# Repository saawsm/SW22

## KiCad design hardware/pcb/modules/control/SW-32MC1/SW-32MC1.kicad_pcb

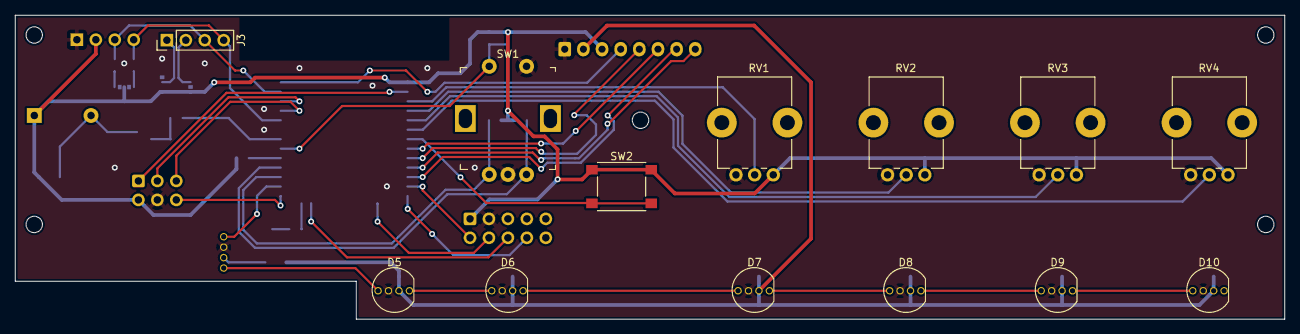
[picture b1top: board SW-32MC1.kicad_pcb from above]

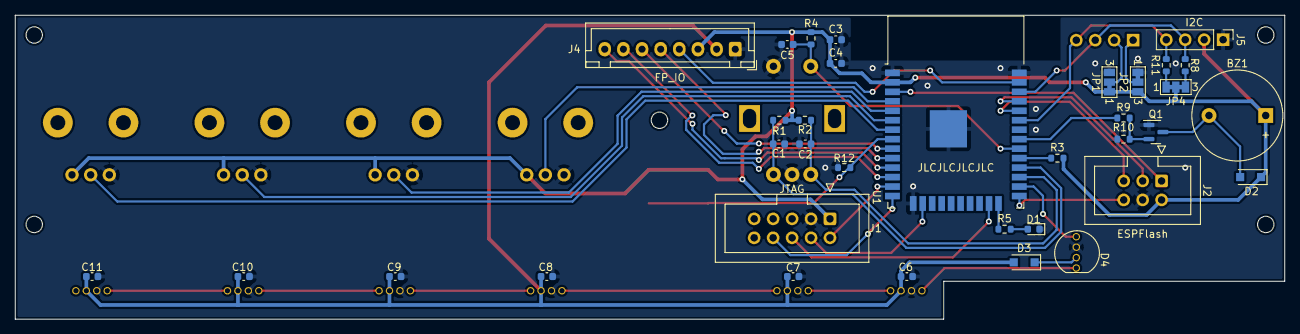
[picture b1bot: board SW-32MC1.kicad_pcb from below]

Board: 2 copper layers, 170.2 x 40.7 mm, 53 parts (35 on the bottom side), 44 nets.

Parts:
BZ1: Buzzer; Buzzer_12x9.5RM7.6
C1, C2, C5: 10nF; C_0603_1608Metric
C3: 10uF; C_0603_1608Metric
C4, C6, C7, C8, C9, C10, C11: 100nF; C_0603_1608Metric
D1: LED; LED_0603_1608Metric
D2: D_Small; D_SOD-123F
D3: D; D_SOD-123F
D4, D5, D6, D7, D8, D9, D10: WS2812D; WS2812D-F5
H1, H2, H3, H4, H5: MountingHole; MountingHole_2.2mm_M2
J1: JTAG; IDC-Header_2x05_P2.54mm_Vertical
J2: ESPFlash; IDC-Header_2x03_P2.54mm_Vertical
J3: OLED; OLED_I2C_1.3
J4: FP_IO; JST_XH_B8B-XH-A_1x08_P2.50mm_Vertical
J5: I2C; PinHeader_1x04_P2.54mm_Vertical
JP1, JP2: SolderJumper_3_Bridged12; SolderJumper-3_P1.3mm_Bridged12_Pad1.0x1.5mm_NumberLabels
JP4: SolderJumper_3_Bridged123; SolderJumper-3_P1.3mm_Bridged123_Pad1.0x1.5mm_NumberLabels
Q1: Q_NMOS_DGS; SOT-23
R1, R2, R4, R10, R12: 10K; R_0603_1608Metric
R3, R5: 10k; R_0603_1608Metric
R8, R11: 2.7K; R_0603_1608Metric
R9: 10; R_0603_1608Metric
RV1, RV2, RV3, RV4: 20K; Potentiometer_Bourns_PTV09A-1_Single_Vertical
SW1: PEC11R-4225F-S0024; Rotary_Encoder_Switched_PEC11R
SW2: DNP; SW_Push_1P1T_NO_6x6mm_H9.5mm
U1: ESP32-WROOM-32D; ESP32-WROOM-32

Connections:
+3V3: BZ1.1 (-), C3.1, C4.1, D2.1 (K), J1.1, J2.2, J4.3, J5.2, JP1.1 (A), JP2.3 (B), JP4.2 (C), R1.1, R2.1, R3.2, R4.1, RV1.1, RV2.1, RV3.1, RV4.1, SW2.1, U1.2 (VDD)
+5V: C6.2, C7.2, C8.2, C9.2, C10.2, C11.2, D3.2 (A), D5.2 (VCC), D6.2 (VCC), D7.2 (VCC), D8.2 (VCC), D9.2 (VCC), D10.2 (VCC), J4.2
/BUZZER: R9.1, U1.31 (IO19)
/EN: J2.1, U1.3 (EN)
/ENC_A: C2.1, R2.2, SW1.A, U1.27 (IO16)
/ENC_B: C1.1, R1.2, SW1.B, U1.28 (IO17)
/ENC_SW: C5.1, R4.2, SW1.S1, U1.30 (IO18)
/IO0: J2.6, U1.25 (IO0)
/IO2: R5.1, U1.24 (IO2)
/IO5: R3.1, U1.29 (IO5)
/LED_DATA: D4.4 (DIN), U1.26 (IO4)
/LINE_LEFT: J4.7, U1.12 (IO27)
/LINE_RIGHT: J4.6, U1.9 (IO33)
/LVL_A: RV1.2, U1.4 (SENSOR_VP)
/LVL_B: RV2.2, U1.5 (SENSOR_VN)
/LVL_C: RV3.2, U1.6 (IO34)
/LVL_D: RV4.2, U1.7 (IO35)
/MAIN_SCL: J4.4, U1.37 (IO23)
/MAIN_SDA: J4.5, U1.10 (IO25)
/MIC: J4.8, U1.11 (IO26)
/MTCK: J1.4, U1.16 (IO13)
/MTDI: J1.8, U1.14 (IO12)
/MTDO: J1.6, U1.23 (IO15)
/MTMS: J1.2, U1.13 (IO14)
/RXD: J2.5, U1.34 (RXD0/IO3)
/SCL: J3.3 (SCL), J5.3, R8.2, U1.36 (IO22)
/SDA: J3.4 (SDA), J5.4, R11.2, U1.33 (IO21)
/SW1: R12.1, SW2.2, U1.8 (IO32)
/TXD: J2.3, U1.35 (TXD0/IO1)
GND: C1.2, C2.2, C3.2, C4.2, C5.2, C6.1, C7.1, C8.1, C9.1, C10.1, C11.1, D1.1 (K), D4.3 (GND), D5.3 (GND), D6.3 (GND), D7.3 (GND), D8.3 (GND), D9.3 (GND), D10.3 (GND), J1.3, J2.4, J4.1, J5.1, JP1.3 (B), JP2.1 (A), Q1.1 (S), R10.2, R12.2, RV1.3, RV2.3, RV3.3, RV4.3, SW1.C, SW1.S2, U1.1 (GND), U1.15 (GND), U1.38 (GND), U1.39 (GND)
unnamed: BZ1.2 (+), D2.2 (A), Q1.3 (D)
unnamed: D1.2 (A), R5.2
unnamed: D3.1 (K), D4.2 (VCC)
unnamed: D4.1 (DOUT), D5.4 (DIN)
unnamed: D5.1 (DOUT), D6.4 (DIN)
unnamed: D6.1 (DOUT), D7.4 (DIN)
unnamed: D7.1 (DOUT), D8.4 (DIN)
unnamed: D8.1 (DOUT), D9.4 (DIN)
unnamed: D9.1 (DOUT), D10.4 (DIN)
unnamed: J3.1 (GND), JP2.2 (C)
unnamed: J3.2 (VCC), JP1.2 (C)
unnamed: JP4.1 (A), R11.1
unnamed: JP4.3 (B), R8.1
unnamed: Q1.2 (G), R9.2, R10.1

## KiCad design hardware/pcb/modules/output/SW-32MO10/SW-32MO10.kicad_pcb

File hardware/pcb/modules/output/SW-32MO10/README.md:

# SW-32MO10 - 1 Channel Output Module

## About
This is a single channel e-stim output module. It tries to mimic the output stage of the well-known Erostec ET312, or better, the MK-312.

The original design of this module was based on the design by [WendyTeslaburger/WT-312](https://github.com/WendyTeslaburger/WT-312).

## Status
- [x] Create v1.1 Schematic
- [ ] Route v1.1 PCB
- [ ] Order v1.1 PCBs
- [ ] Review 

## Gerber & Bill of Materials (BOM)
The Gerber zip file was generated with [JLCPCB](https://jlcpcb.com/) in mind (excluding assembly).
Two BOM sources are available, the interactive HTML BOM located in `/bom` folder, and a CSV file.

### Excluded BOM Items:
- 0.1" break-away pin headers/sockets
- Misc connectors

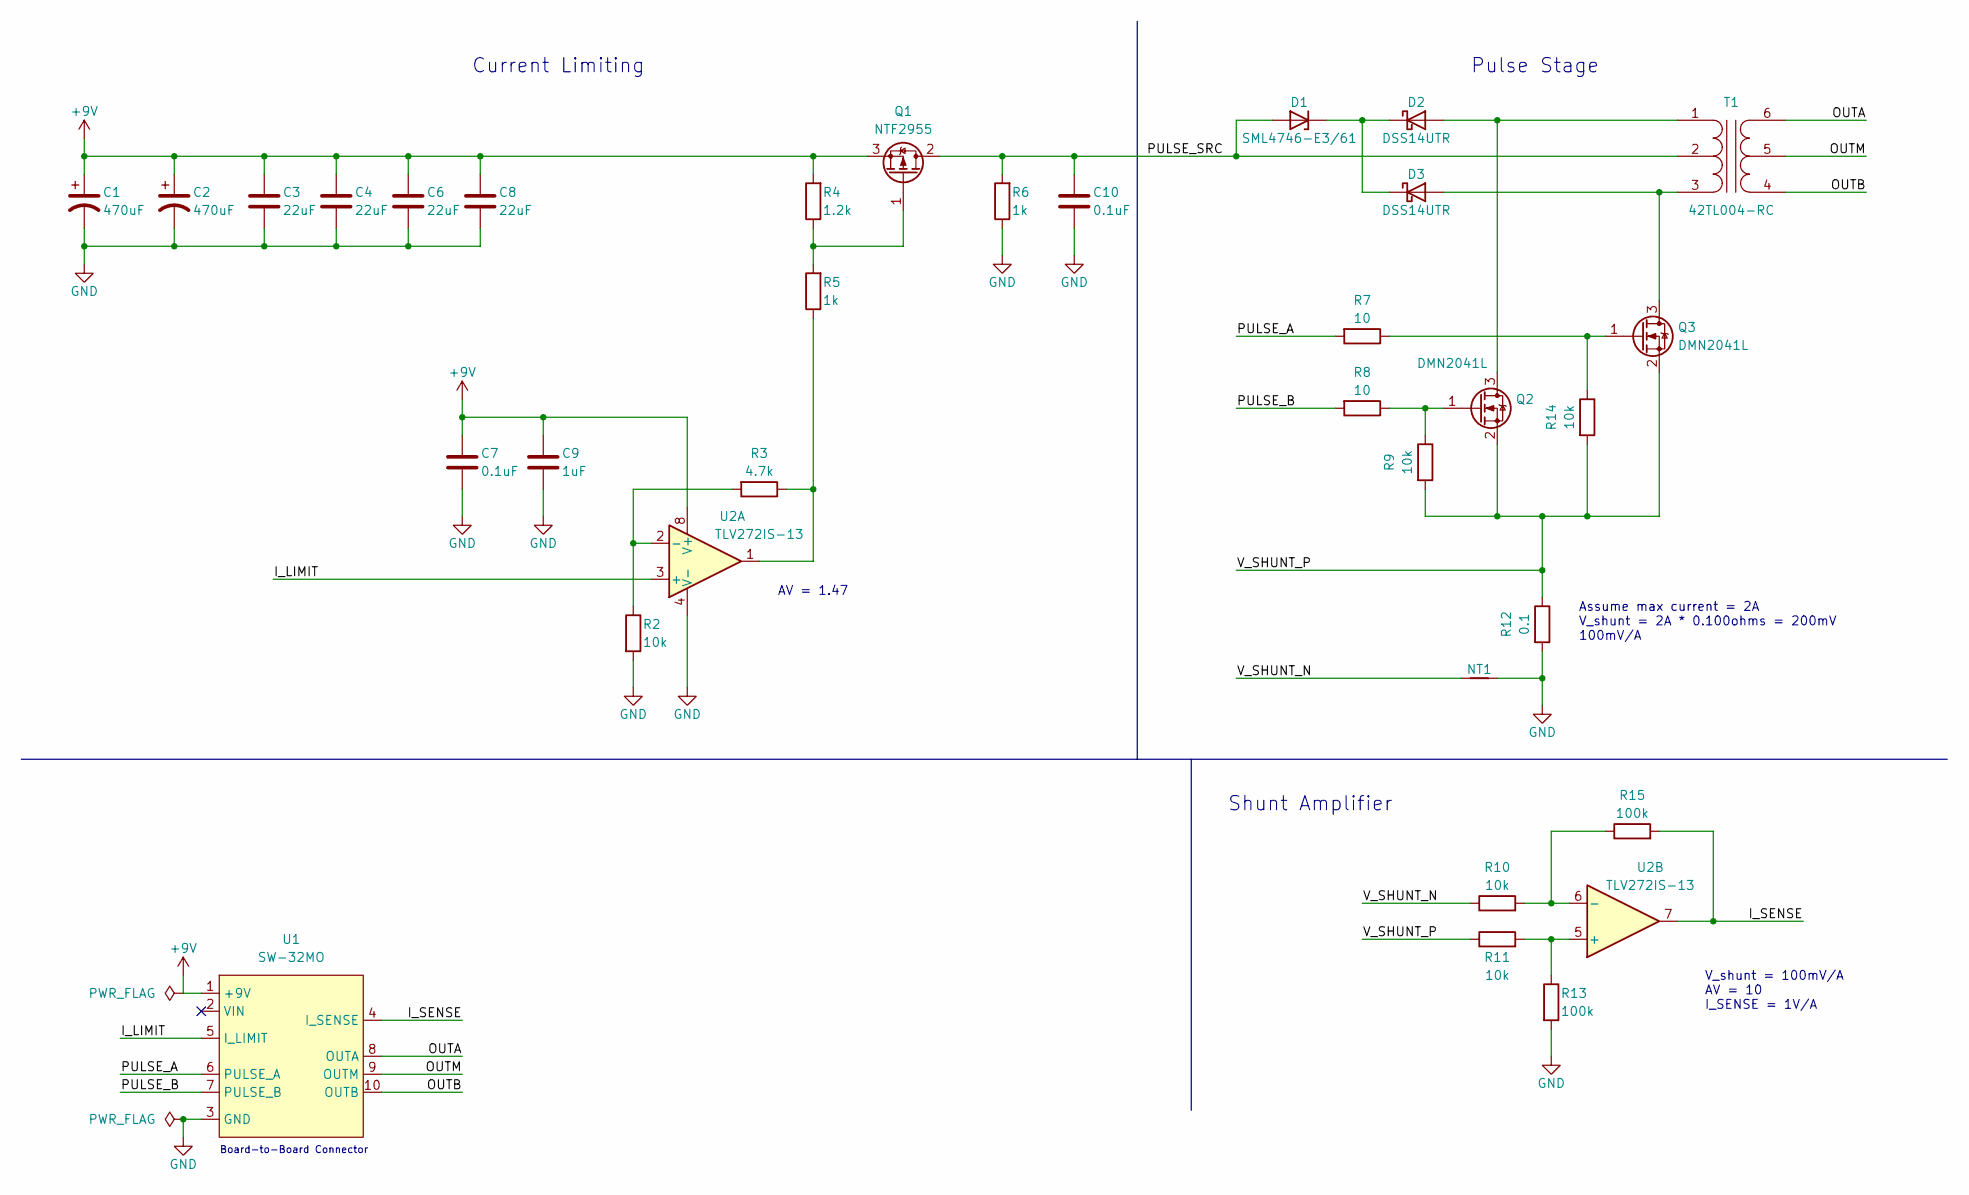
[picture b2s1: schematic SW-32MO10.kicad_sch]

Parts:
C1, C2: 470uF; CP_Radial_D8.0mm_P3.50mm; MPN 477CKE016M
C3, C4, C6, C8: 22uF; C_1210_3225Metric; MPN 12103D226MAT2A
C7, C10: 0.1uF; C_0603_1608Metric; MPN CL10B104KB8NNWC
C9: 1uF; C_0603_1608Metric; MPN CL10B105KA8NFNC
D1: SML4746-E3/61; D_SMA; MPN SML4746-E3/61
D2, D3: DSS14UTR; D_SOD-123F; MPN DSS14UTR
NT1: NetTie_2; NetTie-2_SMD_Pad0.5mm
Q1: NTF2955; SOT-223-3_TabPin2; MPN NTF2955T1G
Q2, Q3: DMN2041L; SOT-23; MPN DMN2041L-7
R2, R9, R10, R11, R14: 10k; R_0603_1608Metric; MPN RC0603FR-0710KL
R3: 4.7k; R_0603_1608Metric; MPN RC0603FR-074K7L
R4: 1.2k; R_0603_1608Metric; MPN RC0603FR-071K2L
R5, R6: 1k; R_0603_1608Metric; MPN AC0603FR-101KL
R7, R8: 10; R_0603_1608Metric; MPN RC0603FR-0710RL
R12: 0.1; R_1206_3216Metric; MPN SCRR1206S1-R100F
R13, R15: 100k; R_0603_1608Metric; MPN RC0603FR-07100KL
T1: 42TL004-RC; 42TL; MPN 42TL004-RC
U1: SW-32MO; SW-32MO_Header
U2: TLV272IS-13; SOIC-8_3.9x4.9mm_P1.27mm; MPN TLV272IS-13

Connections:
+9V: C1.1, C2.1, C3.1, C4.1, C6.1, C7.1, C8.1, C9.1, Q1.3 (S), R4.2, U1.1 (+9V), U2.8 (V+)
/I_LIMIT: U1.5 (I_LIMIT), U2.3 (+)
/I_SENSE: R15.2, U1.4 (I_SENSE), U2.7
/OUTA: T1.6 (S2), U1.8 (OUTA)
/OUTB: T1.4 (S1), U1.10 (OUTB)
/OUTM: T1.5 (SM), U1.9 (OUTM)
/PULSE_A: R7.2, U1.6 (PULSE_A)
/PULSE_B: R8.2, U1.7 (PULSE_B)
/PULSE_SRC: C10.1, D1.2 (A), Q1.2 (D), R6.2, T1.2 (PM)
/V_SHUNT_N: NT1.1, R10.1
/V_SHUNT_P: Q2.2 (S), Q3.2 (S), R9.2, R11.1, R12.1, R14.2
GND: C1.2, C2.2, C3.2, C4.2, C6.2, C7.2, C8.2, C9.2, C10.2, NT1.2, R2.2, R6.1, R12.2, R13.2, U1.3 (GND), U2.4 (V-)
unnamed: D1.1 (K), D2.1 (K), D3.1 (K)
unnamed: D2.2 (A), Q2.3 (D), T1.1 (PR1)
unnamed: D3.2 (A), Q3.3 (D), T1.3 (PR2)
unnamed: Q1.1 (G), R4.1, R5.2
unnamed: Q2.1 (G), R8.1, R9.1
unnamed: Q3.1 (G), R7.1, R14.1
unnamed: R2.1, R3.2, U2.2 (-)
unnamed: R3.1, R5.1, U2.1
unnamed: R10.2, R15.1, U2.6 (-)
unnamed: R11.2, R13.1, U2.5 (+)

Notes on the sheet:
Assume max current = 2A V_shunt = 2A * 0.100ohms = 200mV 100mV/A
V_shunt = 100mV/A AV = 10 I_SENSE = 1V/A
AV = 1.47
Shunt Amplifier
Pulse Stage
Current Limiting
Board-to-Board Connector

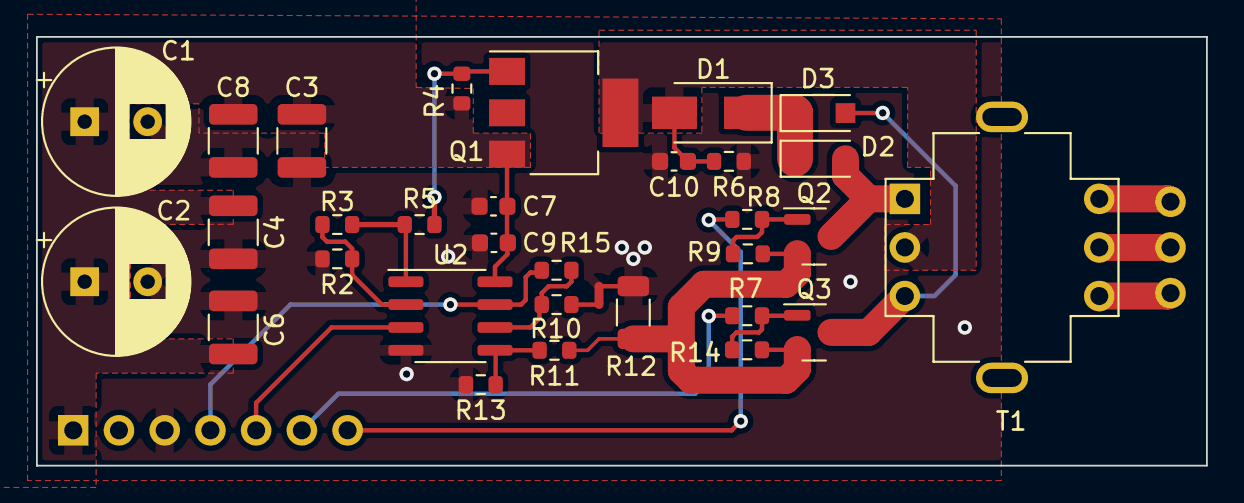
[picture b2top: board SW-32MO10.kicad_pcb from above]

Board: 2 copper layers, 65.0 x 23.8 mm, 33 parts (0 on the bottom side), 22 nets.

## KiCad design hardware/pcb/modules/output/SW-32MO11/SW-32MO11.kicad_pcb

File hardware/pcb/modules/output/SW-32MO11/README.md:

# SW-32MO11 - 1 Channel Output Module

## About
This is a single channel e-stim output module. It tries to mimic the output stage of the well-known Erostec ET312, or better, the MK-312.

The original design of this module was based on the design by [WendyTeslaburger/WT-312](https://github.com/WendyTeslaburger/WT-312).

## Status
- [x] Create v1.0 Schematic
- [ ] Route v1.0 PCB
- [ ] Order v1.0 PCBs
- [ ] Review 

## Gerber & Bill of Materials (BOM)
The Gerber zip file was generated with [JLCPCB](https://jlcpcb.com/) in mind (excluding assembly).
Two BOM sources are available, the interactive HTML BOM located in `/bom` folder, and a CSV file.

### Excluded BOM Items:
- 0.1" break-away pin headers/sockets
- Misc connectors

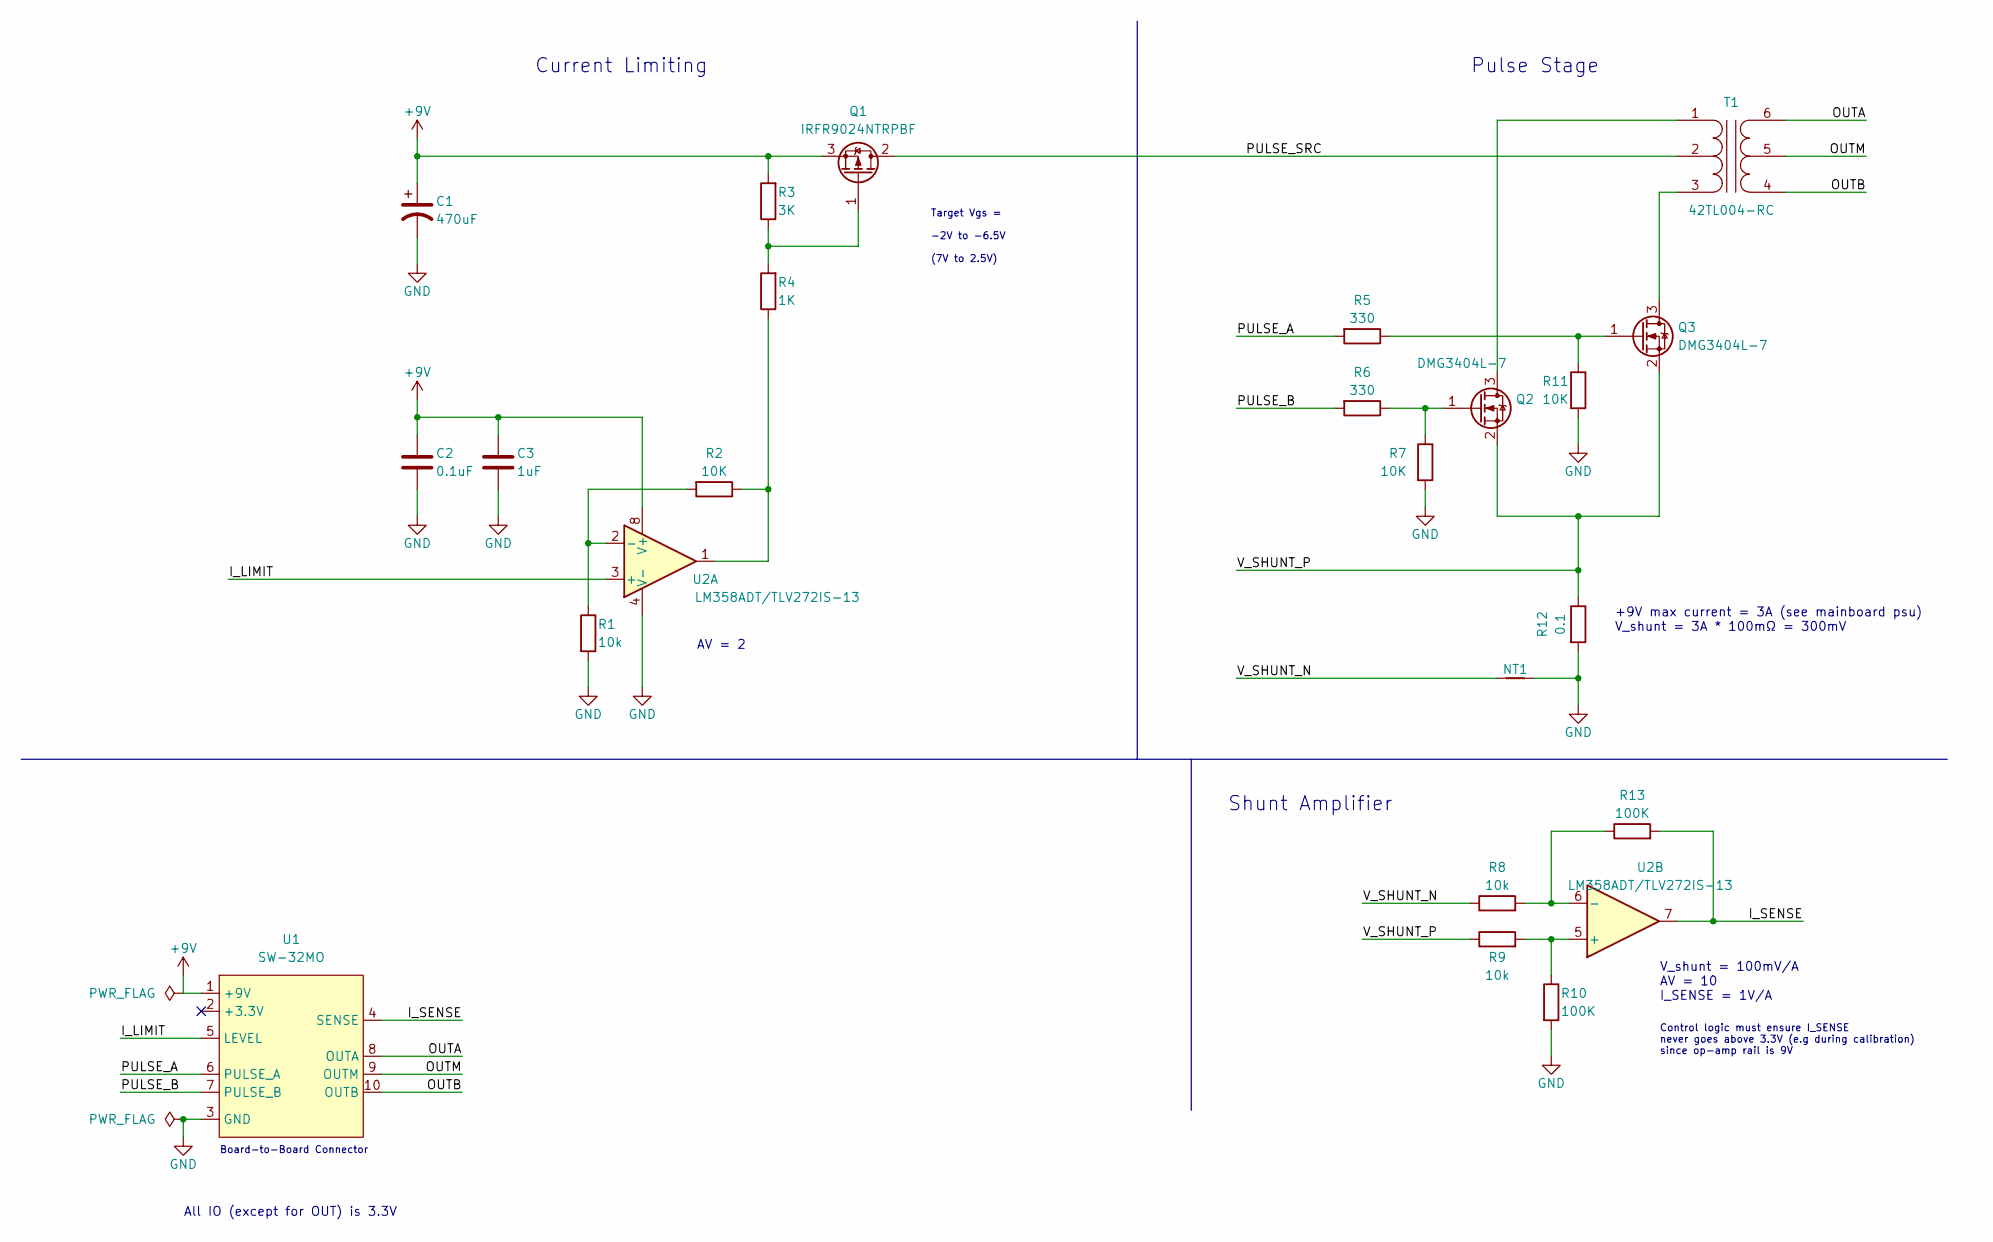
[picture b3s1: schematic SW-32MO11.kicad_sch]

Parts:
C1: 470uF; CP_Radial_D8.0mm_P3.50mm; MPN 477CKE016M
C2: 0.1uF; C_0603_1608Metric; MPN CL10B104KB8NNWC
C3: 1uF; C_0603_1608Metric; MPN CL10B105KA8NFNC
NT1: NetTie_2; NetTie-2_SMD_Pad0.5mm
Q1: IRFR9024NTRPBF; TO-252-3_TabPin2; MPN IRFR9024NTRPBF
Q2, Q3: DMG3404L-7; SOT-23; MPN DMG3404L-7
R1, R8, R9: 10k; R_0603_1608Metric; MPN RC0603FR-0710KL
R2, R7, R11: 10K; R_0603_1608Metric; MPN RC0603FR-0710KL
R3: 3K; R_0603_1608Metric; MPN RC0603FR-073KL
R4: 1K; R_0603_1608Metric; MPN RC0603FR-071KL
R5, R6: 330; R_0603_1608Metric; MPN RC0603FR-07330RL
R10, R13: 100K; R_0603_1608Metric; MPN RC0603FR-07100KL
R12: 0.1; R_1206_3216Metric; MPN ERJ-8BWFR100V
T1: 42TL004-RC; 42TL; MPN 42TL004-RC
U1: SW-32MO; SW-32MO_Header
U2: LM358ADT/TLV272IS-13; SOIC-8_3.9x4.9mm_P1.27mm; MPN TLV272IS-13

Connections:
+9V: C1.1, C2.1, C3.1, Q1.3 (S), R3.2, U1.1 (+9V), U2.8 (V+)
/I_LIMIT: U1.5 (LEVEL), U2.3 (+)
/I_SENSE: R13.2, U1.4 (SENSE), U2.7
/OUTA: T1.6 (S2), U1.8 (OUTA)
/OUTB: T1.4 (S1), U1.10 (OUTB)
/OUTM: T1.5 (SM), U1.9 (OUTM)
/PULSE_A: R5.2, U1.6 (PULSE_A)
/PULSE_B: R6.2, U1.7 (PULSE_B)
/PULSE_SRC: Q1.2 (D), T1.2 (PM)
/V_SHUNT_N: NT1.1, R8.1
/V_SHUNT_P: Q2.2 (S), Q3.2 (S), R9.1, R12.1
GND: C1.2, C2.2, C3.2, NT1.2, R1.2, R7.2, R10.2, R11.2, R12.2, U1.3 (GND), U2.4 (V-)
unnamed: Q1.1 (G), R3.1, R4.2
unnamed: Q2.1 (G), R6.1, R7.1
unnamed: Q2.3 (D), T1.1 (PR1)
unnamed: Q3.1 (G), R5.1, R11.1
unnamed: Q3.3 (D), T1.3 (PR2)
unnamed: R1.1, R2.2, U2.2 (-)
unnamed: R2.1, R4.1, U2.1
unnamed: R9.2, R10.1, U2.5 (+)
unnamed: R8.2, R13.1, U2.6 (-)

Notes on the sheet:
+9V max current = 3A (see mainboard psu) V_shunt = 3A * 100mΩ = 300mV
V_shunt = 100mV/A AV = 10 I_SENSE = 1V/A
AV = 2
Shunt Amplifier
Pulse Stage
Target Vgs = -2V to -6.5V (7V to 2.5V)
Current Limiting
All IO (except for OUT) is 3.3V
Board-to-Board Connector
Control logic must ensure I_SENSE never goes above 3.3V (e.g during calibration) since op-amp rail is 9V

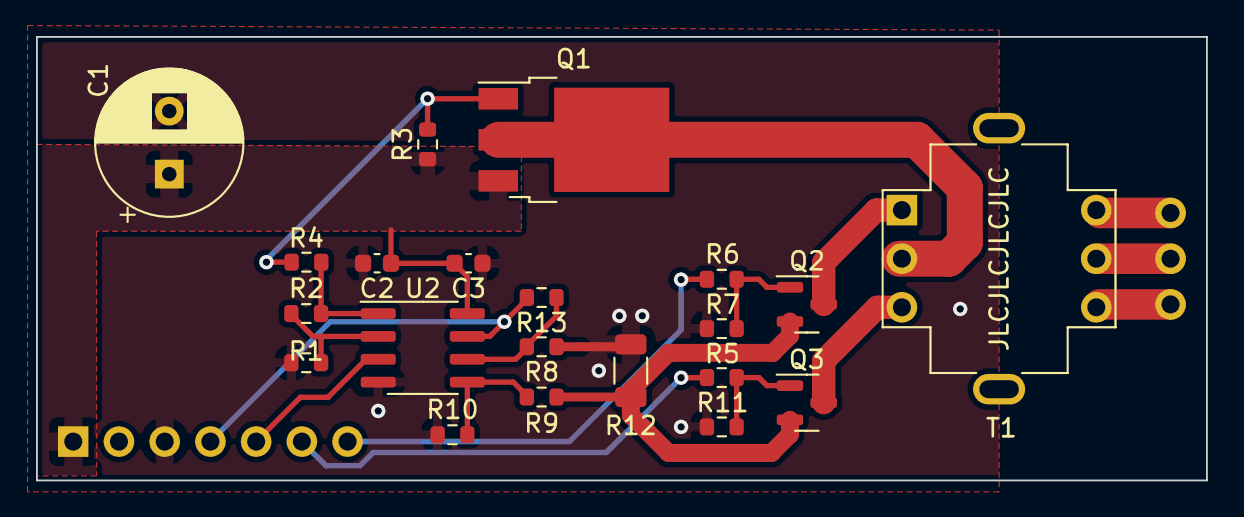
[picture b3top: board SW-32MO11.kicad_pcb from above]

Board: 2 copper layers, 65.0 x 24.6 mm, 23 parts (0 on the bottom side), 21 nets.

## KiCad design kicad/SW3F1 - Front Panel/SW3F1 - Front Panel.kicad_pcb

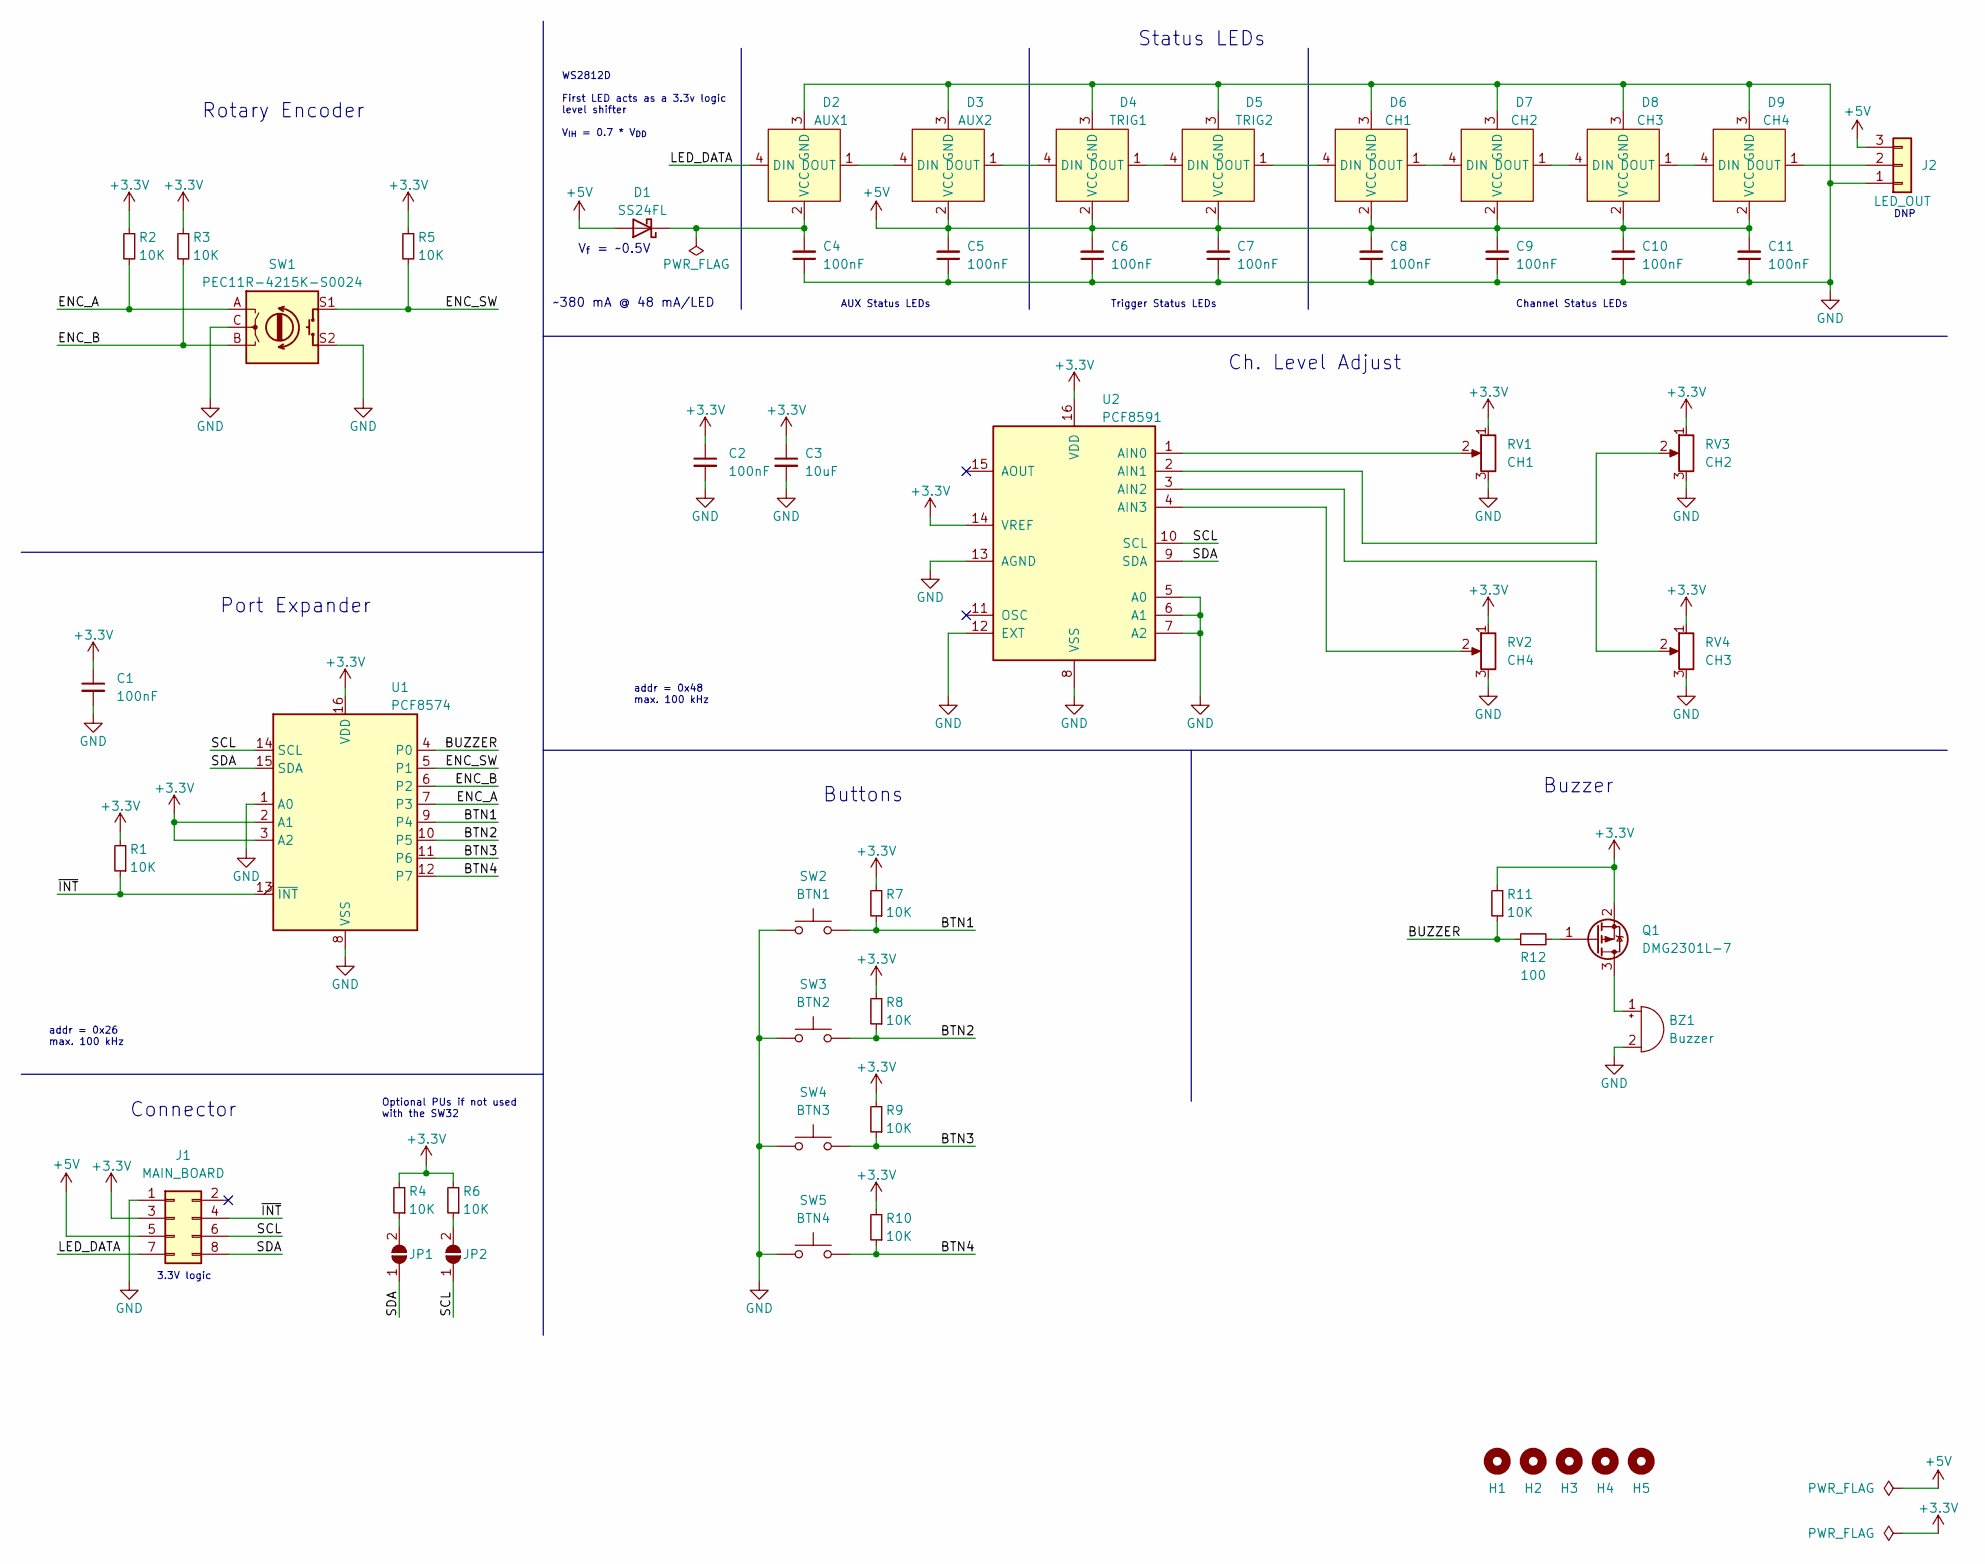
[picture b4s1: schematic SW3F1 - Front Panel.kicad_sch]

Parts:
BZ1: Buzzer; Buzzer_12x9.5RM7.6; MPN IE122303-1; MOUSER 497-IE122303-1
C1, C2, C4, C5, C6, C7, C8, C9, C10, C11: 100nF; C_0603_1608Metric; MPN CL10B104KB8NNNC; LCSC C1591
C3: 10uF; C_0603_1608Metric; MPN CL10A106MA8NRNC; LCSC C96446
D1: SS24FL; D_SOD-123F; MPN SS24FL; MOUSER 512-SS24FL
D2: AUX1; WS2812D-F5; MPN WS2812D-F5; LCSC C190565
D3: AUX2; WS2812D-F5; MPN WS2812D-F5; LCSC C190565
D4: TRIG1; WS2812D-F5; MPN WS2812D-F5; LCSC C190565
D5: TRIG2; WS2812D-F5; MPN WS2812D-F5; LCSC C190565
D6: CH1; WS2812D-F5; MPN WS2812D-F5; LCSC C190565
D7: CH2; WS2812D-F5; MPN WS2812D-F5; LCSC C190565
D8: CH3; WS2812D-F5; MPN WS2812D-F5; LCSC C190565
D9: CH4; WS2812D-F5; MPN WS2812D-F5; LCSC C190565
H1, H2, H3, H4, H5: MountingHole; MountingHole_2.2mm_M2
J1: MAIN_BOARD; IDC-Header_2x04_P2.54mm_Vertical
J2: LED_OUT; PinHeader_1x03_P2.54mm_Vertical
JP1, JP2: SolderJumper_2_Open; SolderJumper-2_P1.3mm_Open_RoundedPad1.0x1.5mm
Q1: DMG2301L-7; SOT-23; MPN DMG2301L-7; LCSC C102619
R1, R2, R3, R4, R5, R6, R7, R8, R9, R10, R11: 10K; R_0603_1608Metric; MPN RC0603FR-0710KL; LCSC C98220
R12: 100; R_0603_1608Metric; MPN RC0603FR-07100RL; MOUSER 603-RC0603FR-07100RL
RV1: CH1; Potentiometer_Bourns_PTV09A-1_Single_Vertical; MPN PTV09A-4020S-B103
RV2: CH4; Potentiometer_Bourns_PTV09A-1_Single_Vertical; MPN PTV09A-4020S-B103
RV3: CH2; Potentiometer_Bourns_PTV09A-1_Single_Vertical; MPN PTV09A-4020S-B103
RV4: CH3; Potentiometer_Bourns_PTV09A-1_Single_Vertical; MPN PTV09A-4020S-B103
SW1: PEC11R-4215K-S0024; Rotary_Encoder_Switched_PEC11R; MPN PEC11R-4215K-S0024
SW2: BTN1; D6C; MPN D6C90F2LFS; MOUSER 611-D6C90F2LFS
SW3: BTN2; D6C; MPN D6C90F2LFS; MOUSER 611-D6C90F2LFS
SW4: BTN3; D6C; MPN D6C90F2LFS; MOUSER 611-D6C90F2LFS
SW5: BTN4; D6C; MPN D6C90F2LFS; MOUSER 611-D6C90F2LFS
U1: PCF8574; SOIC-16W_7.5x10.3mm_P1.27mm; MPN PCF8574T/3,512; LCSC C1522621
U2: PCF8591; SOIC-16W_7.5x10.3mm_P1.27mm; MPN PCF8591T/2,518; MOUSER 771-PCF8591TD-T

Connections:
+3.3V: C1.1, C2.1, C3.1, J1.3, Q1.2 (S), R1.2, R2.1, R3.1, R4.2, R5.1, R6.2, R7.2, R8.2, R9.2, R10.2, R11.2, RV1.1, RV2.1, RV3.1, RV4.1, U1.2 (A1), U1.3 (A2), U1.16 (VDD), U2.14 (VREF), U2.16 (VDD); also elsewhere on the board
+5V: C5.2, C6.2, C7.2, C8.2, C9.2, C10.2, C11.2, D1.2 (A), D3.2 (VCC), D4.2 (VCC), D5.2 (VCC), D6.2 (VCC), D7.2 (VCC), D8.2 (VCC), D9.2 (VCC), J1.5, J2.3
/BTN1: R7.1, SW2.2, U1.9 (P4)
/BTN2: R8.1, SW3.2, U1.10 (P5); also elsewhere on the board
/BTN3: R9.1, SW4.2, U1.11 (P6)
/BTN4: R10.1, SW5.2, U1.12 (P7)
/BUZZER: R11.1, R12.1, U1.4 (P0)
/ENC_A: R2.2, SW1.A, U1.7 (P3)
/ENC_B: R3.2, SW1.B, U1.6 (P2)
/ENC_SW: R5.2, SW1.S1, U1.5 (P1)
/LED_DATA: D2.4 (DIN), J1.7
/SCL: J1.6, JP2.1 (A), U1.14 (SCL), U2.10 (SCL)
/SDA: J1.8, JP1.1 (A), U1.15 (SDA), U2.9 (SDA)
/~INT: J1.4, R1.1, U1.13 (~INT)
GND: BZ1.2 (+), C1.2, C2.2, C3.2, C4.1, C5.1, C6.1, C7.1, C8.1, C9.1, C10.1, C11.1, D2.3 (GND), D3.3 (GND), D4.3 (GND), D5.3 (GND), D6.3 (GND), D7.3 (GND), D8.3 (GND), D9.3 (GND), J1.1, J2.1, RV1.3, RV2.3, RV3.3, RV4.3, SW1.C, SW1.S2, SW2.1, SW3.1, SW4.1, SW5.1, U1.1 (A0), U1.8 (VSS), U2.5 (A0), U2.6 (A1), U2.7 (A2), U2.8 (VSS), U2.12 (EXT), U2.13 (AGND)
unnamed: BZ1.1 (-), Q1.3 (D)
unnamed: C4.2, D1.1 (K), D2.2 (VCC)
unnamed: D2.1 (DOUT), D3.4 (DIN)
unnamed: D3.1 (DOUT), D4.4 (DIN)
unnamed: D4.1 (DOUT), D5.4 (DIN)
unnamed: D5.1 (DOUT), D6.4 (DIN)
unnamed: D6.1 (DOUT), D7.4 (DIN)
unnamed: D7.1 (DOUT), D8.4 (DIN)
unnamed: D8.1 (DOUT), D9.4 (DIN)
unnamed: D9.1 (DOUT), J2.2
unnamed: JP1.2 (B), R4.1
unnamed: JP2.2 (B), R6.1
unnamed: Q1.1 (G), R12.2
unnamed: RV1.2, U2.1 (AIN0)
unnamed: RV2.2, U2.4 (AIN3)
unnamed: RV3.2, U2.2 (AIN1)
unnamed: RV4.2, U2.3 (AIN2)

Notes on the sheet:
~380 mA @ 48 mA/LED
Channel Status LEDs
AUX Status LEDs
Ch. Level Adjust
3.3V logic
Port Expander
Buttons
DNP
Status LEDs
Optional PUs if not used with the SW32
addr = 0x48 max. 100 kHz
V_{f} = ~0.5V
Trigger Status LEDs
Buzzer
Rotary Encoder
Connector
addr = 0x26 max. 100 kHz
WS2812D First LED acts as a 3.3v logic level shifter V_{IH} = 0.7 * V_{DD}

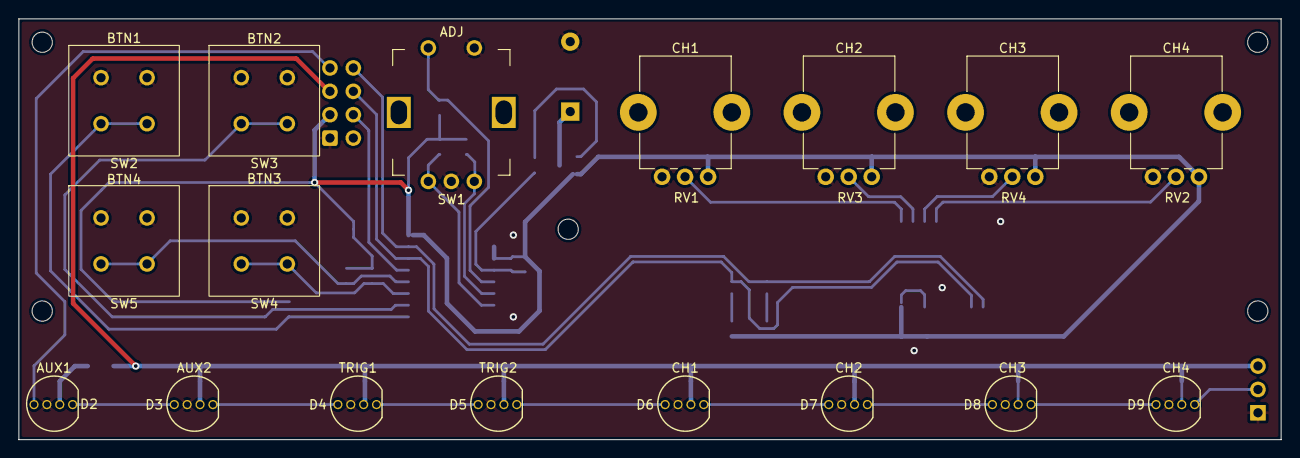
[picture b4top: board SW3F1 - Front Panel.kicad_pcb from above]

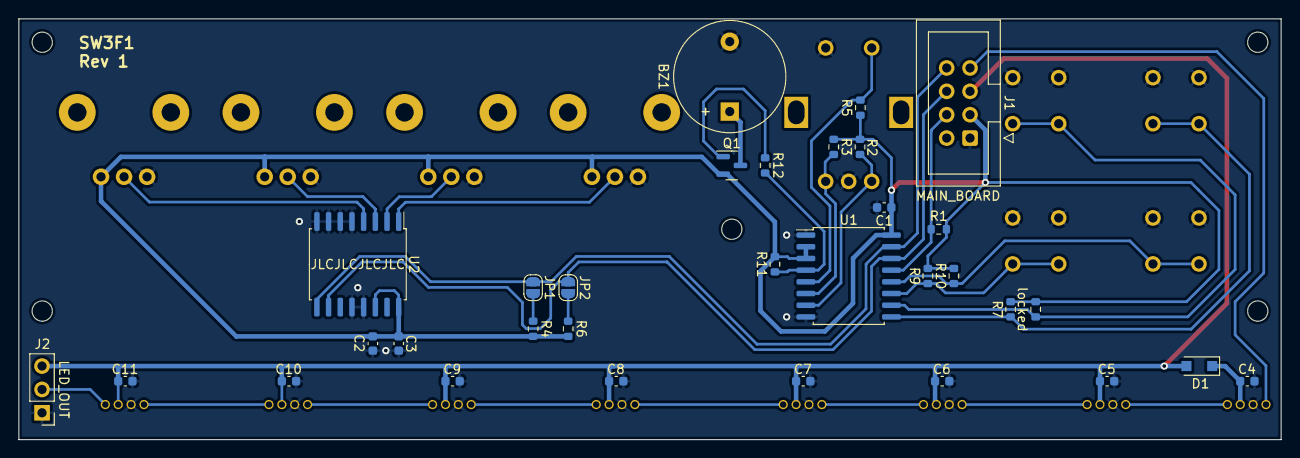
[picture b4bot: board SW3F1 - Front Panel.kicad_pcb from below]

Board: 2 copper layers, 137.2 x 45.7 mm, 54 parts (32 on the bottom side), 32 nets.

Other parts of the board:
locked: 10K; R_0603_1608Metric

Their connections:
+3.3V: locked.2; also elsewhere on the board
/BTN2: locked.1; also elsewhere on the board
